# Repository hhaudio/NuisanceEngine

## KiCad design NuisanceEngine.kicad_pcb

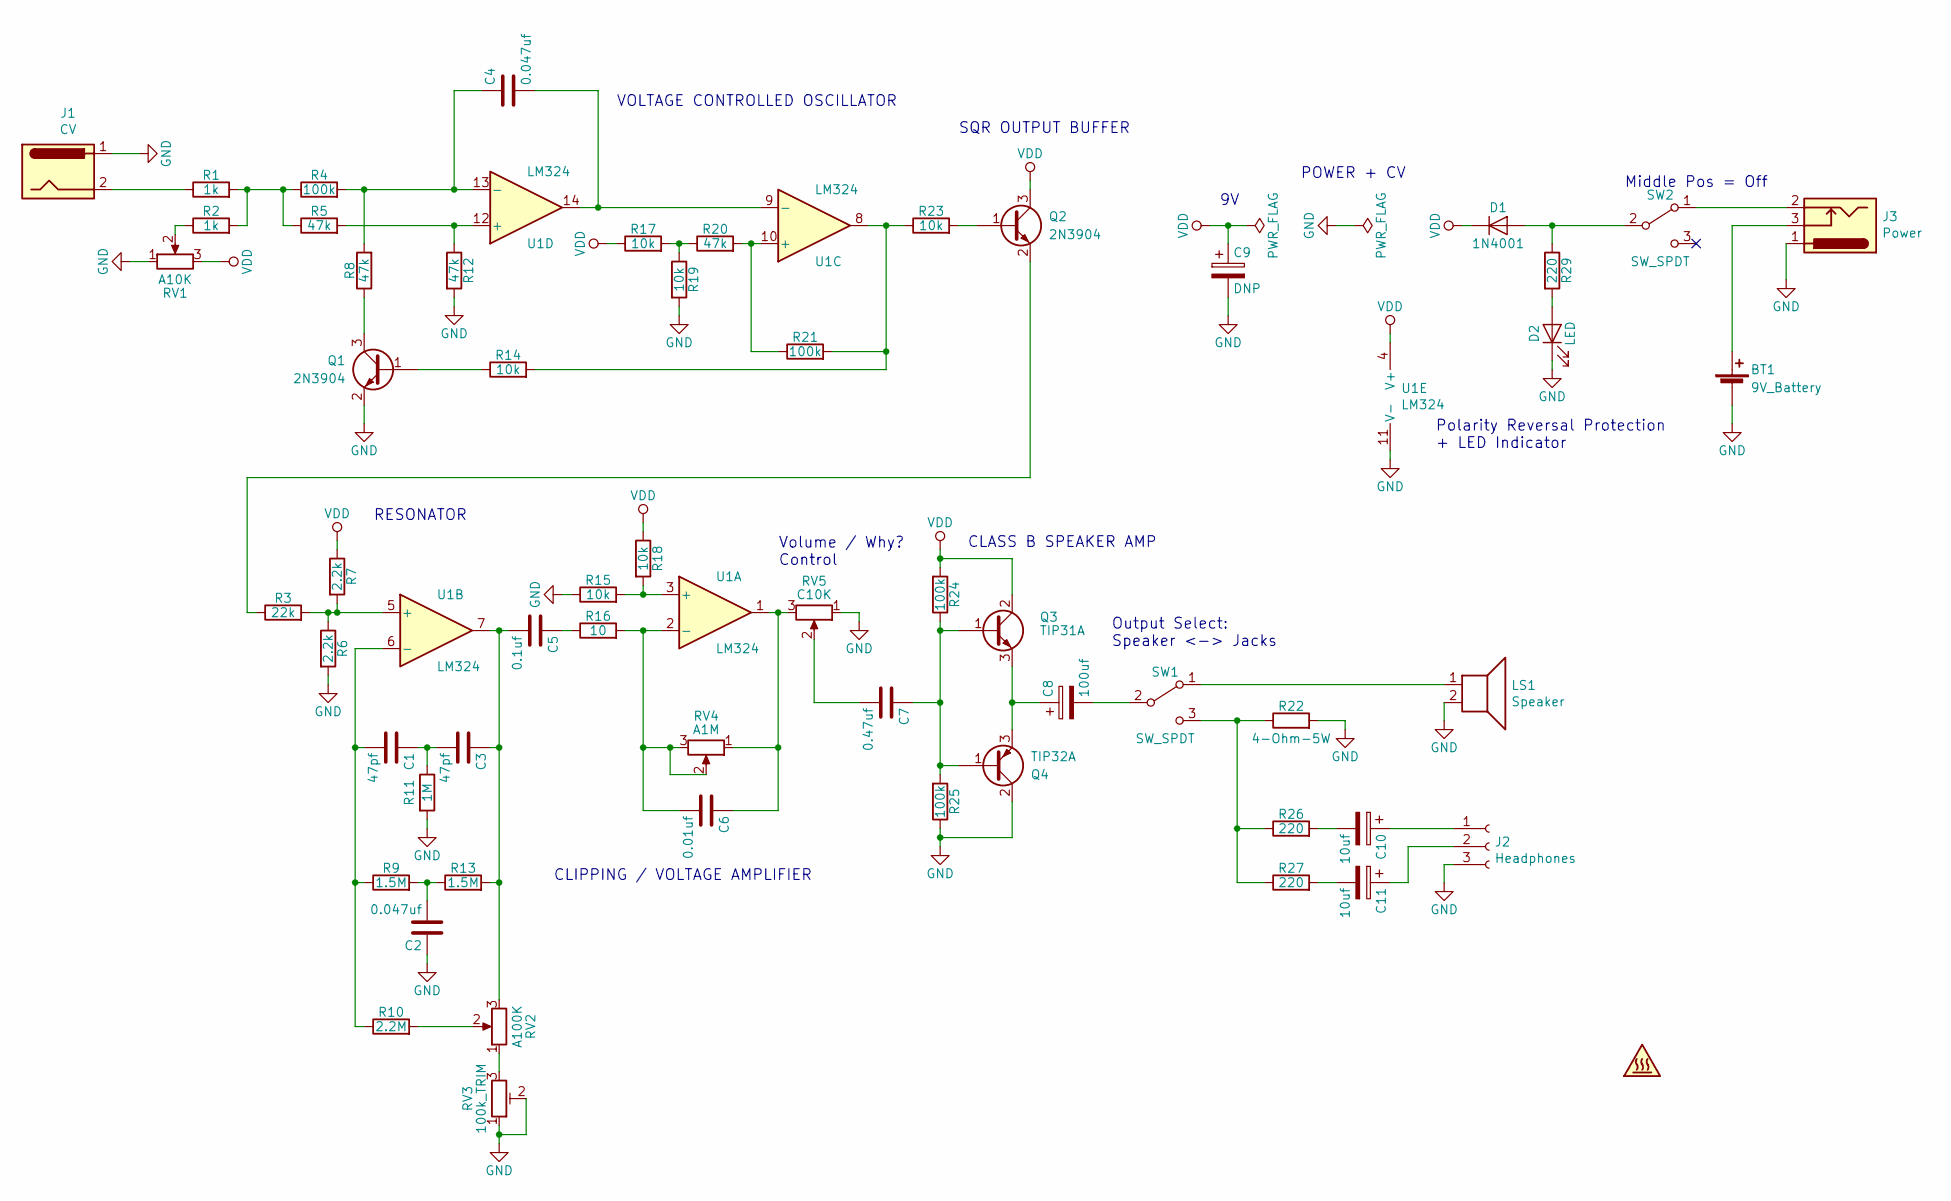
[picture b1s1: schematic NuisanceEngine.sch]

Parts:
BT1: 9V_Battery; 9V_Clip
C1, C3: 47pf; C_0603_1608Metric_Pad1.05x0.95mm_HandSolder
C2, C4: 0.047uf; C_0603_1608Metric_Pad1.05x0.95mm_HandSolder
C5: 0.1uf; C_0603_1608Metric_Pad1.05x0.95mm_HandSolder
C6: 0.01uf; C_0603_1608Metric_Pad1.05x0.95mm_HandSolder
C7: 0.47uf; C_0805_2012Metric_Pad1.15x1.40mm_HandSolder
C8: 100uf; CP_Radial_D6.3mm_P2.50mm
C9: DNP; R_0805_2012Metric_Pad1.15x1.40mm_HandSolder
C10, C11: 10uf; R_0805_2012Metric_Pad1.15x1.40mm_HandSolder
D1: 1N4001; D_SMA_Handsoldering
D2: LED; LED-5MM
J1: CV; PinHeader_1x02_P2.54mm_Vertical
J2: Headphones; PinHeader_1x03_P2.54mm_Vertical
J3: Power; PinHeader_1x03_P2.54mm_Vertical
LS1: Speaker; PinHeader_1x02_P2.54mm_Vertical
Q1, Q2: 2N3904; SOT-23_Handsoldering
Q3: TIP31A; TO-220-3_Horizontal_TabDown
Q4: TIP32A; TO-220-3_Horizontal_TabDown
R1, R2: 1k; R_0603_1608Metric_Pad1.05x0.95mm_HandSolder
R3: 22k; R_0603_1608Metric_Pad1.05x0.95mm_HandSolder
R4, R21, R24, R25: 100k; R_0603_1608Metric_Pad1.05x0.95mm_HandSolder
R5, R8, R12, R20: 47k; R_0603_1608Metric_Pad1.05x0.95mm_HandSolder
R6, R7: 2.2k; R_0603_1608Metric_Pad1.05x0.95mm_HandSolder
R9, R13: 1.5M; R_0603_1608Metric_Pad1.05x0.95mm_HandSolder
R10: 2.2M; R_0603_1608Metric_Pad1.05x0.95mm_HandSolder
R11: 1M; R_0603_1608Metric_Pad1.05x0.95mm_HandSolder
R14, R15, R17, R18, R19, R23: 10k; R_0603_1608Metric_Pad1.05x0.95mm_HandSolder
R16: 10; R_0603_1608Metric_Pad1.05x0.95mm_HandSolder
R22: 4-Ohm-5W; Resistor_Vishay5W
R26, R27, R29: 220; R_0603_1608Metric_Pad1.05x0.95mm_HandSolder
RV1: A10K; Alpha_Pot_16MM
RV2: A100K; Alpha_Pot_16MM
RV3: 100k_TRIM; Potentiometer_Trimmer_Piher_PT-6v_Horizontal
RV4: A1M; Alpha_Pot_16MM
RV5: C10K; Alpha_Pot_16MM
SW1, SW2: SW_SPDT; Toggle_3Lug
U1: LM324; DIP-14_W7.62mm

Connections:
GND: BT1.2 (-), C2.1, C9.2, D2.1 (K), J1.1, J2.3, J3.1, LS1.2, Q1.2 (E), Q4.2 (C), R6.2, R11.2, R12.2, R15.1, R19.2, R22.2, R25.1, RV1.1, RV3.1, RV3.2, RV5.1, U1.11 (V-)
unnamed: BT1.1 (+), J3.3
unnamed: C1.1, C3.2, R11.1
unnamed: C1.2, R9.1, R10.1, U1.6 (-)
unnamed: C2.2, R9.2, R13.1
unnamed: C3.1, C5.2, R13.2, RV2.3, U1.7
unnamed: C4.1, R4.2, R8.2, U1.13 (-)
unnamed: C4.2, U1.9 (-), U1.14
unnamed: C5.1, R16.1
unnamed: C6.1, RV4.1, RV5.3, U1.1
unnamed: C6.2, R16.2, RV4.2, RV4.3, U1.2 (-)
unnamed: C7.1, Q3.1 (B), Q4.1 (B), R24.1, R25.2
unnamed: C7.2, RV5.2
unnamed: C8.1, Q3.3 (E), Q4.3 (E)
unnamed: C8.2, SW1.2 (B)
unnamed: C10.1, J2.1
unnamed: C10.2, R26.2
unnamed: C11.1, J2.2
unnamed: C11.2, R27.2
unnamed: D1.2 (A), R29.1, SW2.2 (B)
unnamed: D2.2 (A), R29.2
unnamed: J1.2, R1.1
unnamed: J3.2, SW2.1 (A)
unnamed: LS1.1, SW1.1 (A)
unnamed: Q1.1 (B), R14.1
unnamed: Q1.3 (C), R8.1
unnamed: Q2.1 (B), R23.2
unnamed: Q2.2 (E), R3.1
unnamed: R1.2, R2.2, R4.1, R5.1
unnamed: R2.1, RV1.2
unnamed: R3.2, R6.1, R7.2, U1.5 (+)
unnamed: R10.2, RV2.2
unnamed: R5.2, R12.1, U1.12 (+)
unnamed: R14.2, R21.2, R23.1, U1.8
unnamed: R15.2, R18.2, U1.3 (+)
unnamed: R17.2, R19.1, R20.1
unnamed: R20.2, R21.1, U1.10 (+)
unnamed: R22.1, R26.1, R27.1, SW1.3 (C)
unnamed: RV2.1, RV3.3
VDD: C9.1, D1.1 (K), Q2.3 (C), Q3.2 (C), R7.1, R17.1, R18.1, R24.2, RV1.3, U1.4 (V+)

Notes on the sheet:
VOLTAGE CONTROLLED OSCILLATOR
SQR OUTPUT BUFFER
POWER + CV
RESONATOR
CLIPPING / VOLTAGE AMPLIFIER
CLASS B SPEAKER AMP
Volume / Why? Control
Output Select: Speaker <-> Jacks
Middle Pos = Off
Polarity Reversal Protection + LED Indicator

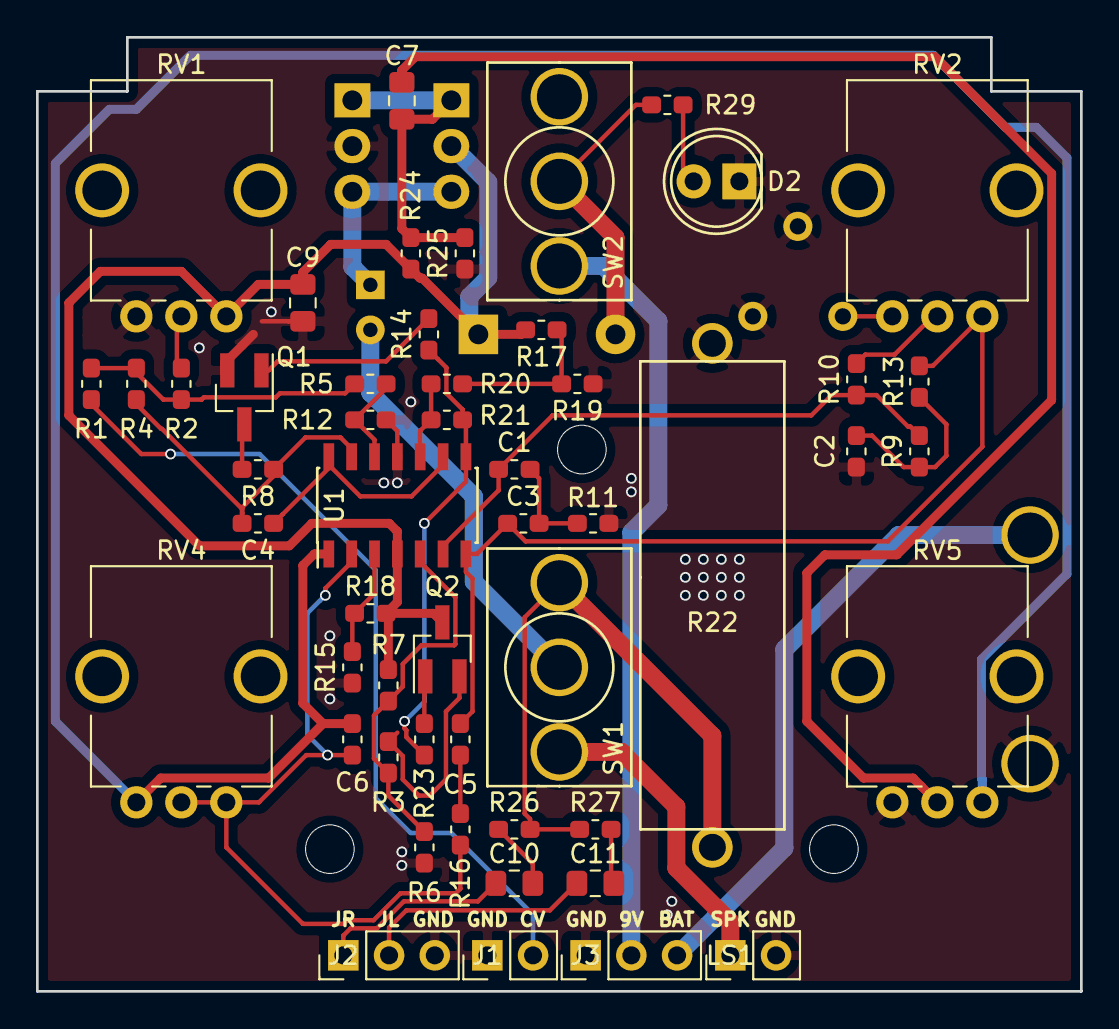
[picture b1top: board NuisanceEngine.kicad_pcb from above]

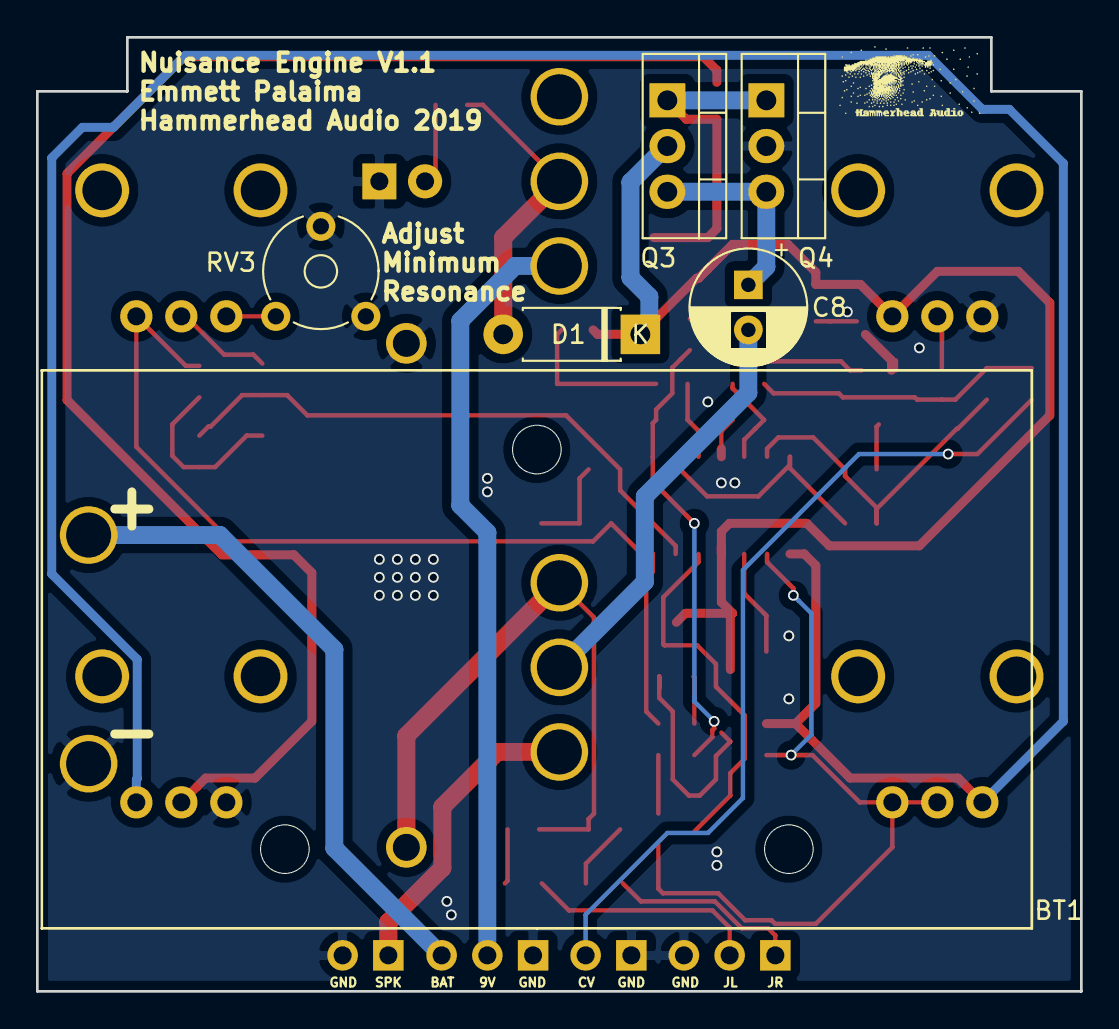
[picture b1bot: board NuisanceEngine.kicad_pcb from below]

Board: 2 copper layers, 58.0 x 53.0 mm, 59 parts (7 on the bottom side), 40 nets.

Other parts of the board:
LOGO: HHLOGO

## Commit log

2018-11-07 Finished schematic, created footprints
2018-11-08 Made footprint for second model of battery holder
2018-11-21 Updated to Kicad 5... Very annoying >:/
2018-11-21 Changed speaker connection
2018-11-21 Updated pin headers
2019-04-05 Started basic layout
2019-04-06 More mushing. Gonna be a mushy one haha
2019-04-06 More mushing
2019-04-18 Commit before trying smt
2019-04-18 Switched to SMT footprints
2019-04-18 Spread components:
2019-04-18 Laid out SMT components, ready for traces
2019-04-18 Dunzo
2019-12-27 Commit before changing pot footprint
2019-12-28 new pot footprint
2019-12-28 gonna rearrange shit to allow for clean transistor placement
2019-12-28 finished new layout, gonna double check tomorrow morning
2019-12-28 moved trimpot from under potentiometer
2019-12-28 Made gerbers
